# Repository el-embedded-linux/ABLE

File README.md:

PROJECT ABLE(Always Bicycle LifE)
=============================

Cycling is a great exercise. However, riding byclces outdoor is sometimes dangerous and difficult due to a bad weather or lack of bike infrastructures. Our project starts to solve those problems. We make a smart bicycle kit which can be equipped on a bicycle and let people can ride it both indoor and outdoor safely. With our kit incorporates Arduino, Raspberry Pi and VR, you can enjoy cycling anytime, anywhere.

When indoors, you can ride your bike fixed by rollers using VR. A lead switch and a pressure seonsor of Arduino deliver state of the bike to VR. When outdoors, you can use matrix LEDs and bar LEDs to use turn signal lights, so that you can ride more safely. In addition, this can replace smart phone applications, which provide unncessary information about bicycles, as ring LEDs and OLEDs can navigate or display speed, time, group riding information, heart rating etc. You can also prevent bike thefts by turning on and off your kit with fingerprint identification security system.

 youtube link

Field
-------------------
 - [IoT](https://github.com/Moerai/2018EL/tree/master/IoT)
 - [VR](https://github.com/Moerai/2018EL/tree/master/VR)
 - [Android](https://github.com/Moerai/2018EL/tree/master/android)

Thank you for your interest in our project.

This project is owned by the club EL of Dongyang Mirae University.

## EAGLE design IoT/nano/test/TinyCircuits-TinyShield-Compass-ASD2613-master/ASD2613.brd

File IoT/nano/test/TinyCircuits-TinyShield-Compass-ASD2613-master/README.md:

# TinyCircuits TinyShield Compass Board
# ASD2613 Rev1

These are the design files for the TinyCircuits ASD2613 Rev 1 PCB.  This is a TinyShield board (Square Version, 20mm x 20mm, or Circular 20mm diameter) that has a Honeywell HMC5883L compass, local power supply and level shifters to connect between the TinyDuino and the accelerometer. 

Format is in Cadsoft Eagle format - Eagle version 6.2 was used for the original design.

For more infomation on this, check out the product page at Tiny-Circuits.com:  https://tiny-circuits.com/tiny-shield-compass.html

#License:

Design by TinyCircuits.
All design files are released under the Creative Commons Attribution Share-Alike 3.0 License, see the following link for details: http://creativecommons.org/licenses/by-sa/3.0

All text above must be included in any redistribution or derived design

This project uses designs and concepts developed as part of the Arduino project and the LilyPad project.  The TinyCircuits design files themselves (schematics, PCB and libraries) are not directly derived from these works' design files and have been created new, however the concepts and basic architecture behind the TinyDuino and TinyLily products are derived and we thank the hard work of the organizations below for their contributions to open-source hardware:
  
Original Arduino Uno Design by Team Arduino

LilyPad Arduino Design by Leah Buechley and Sparkfun Electronics

Please support the open-source hardware community 

3? ????? Compass Value? ??? ??? ???

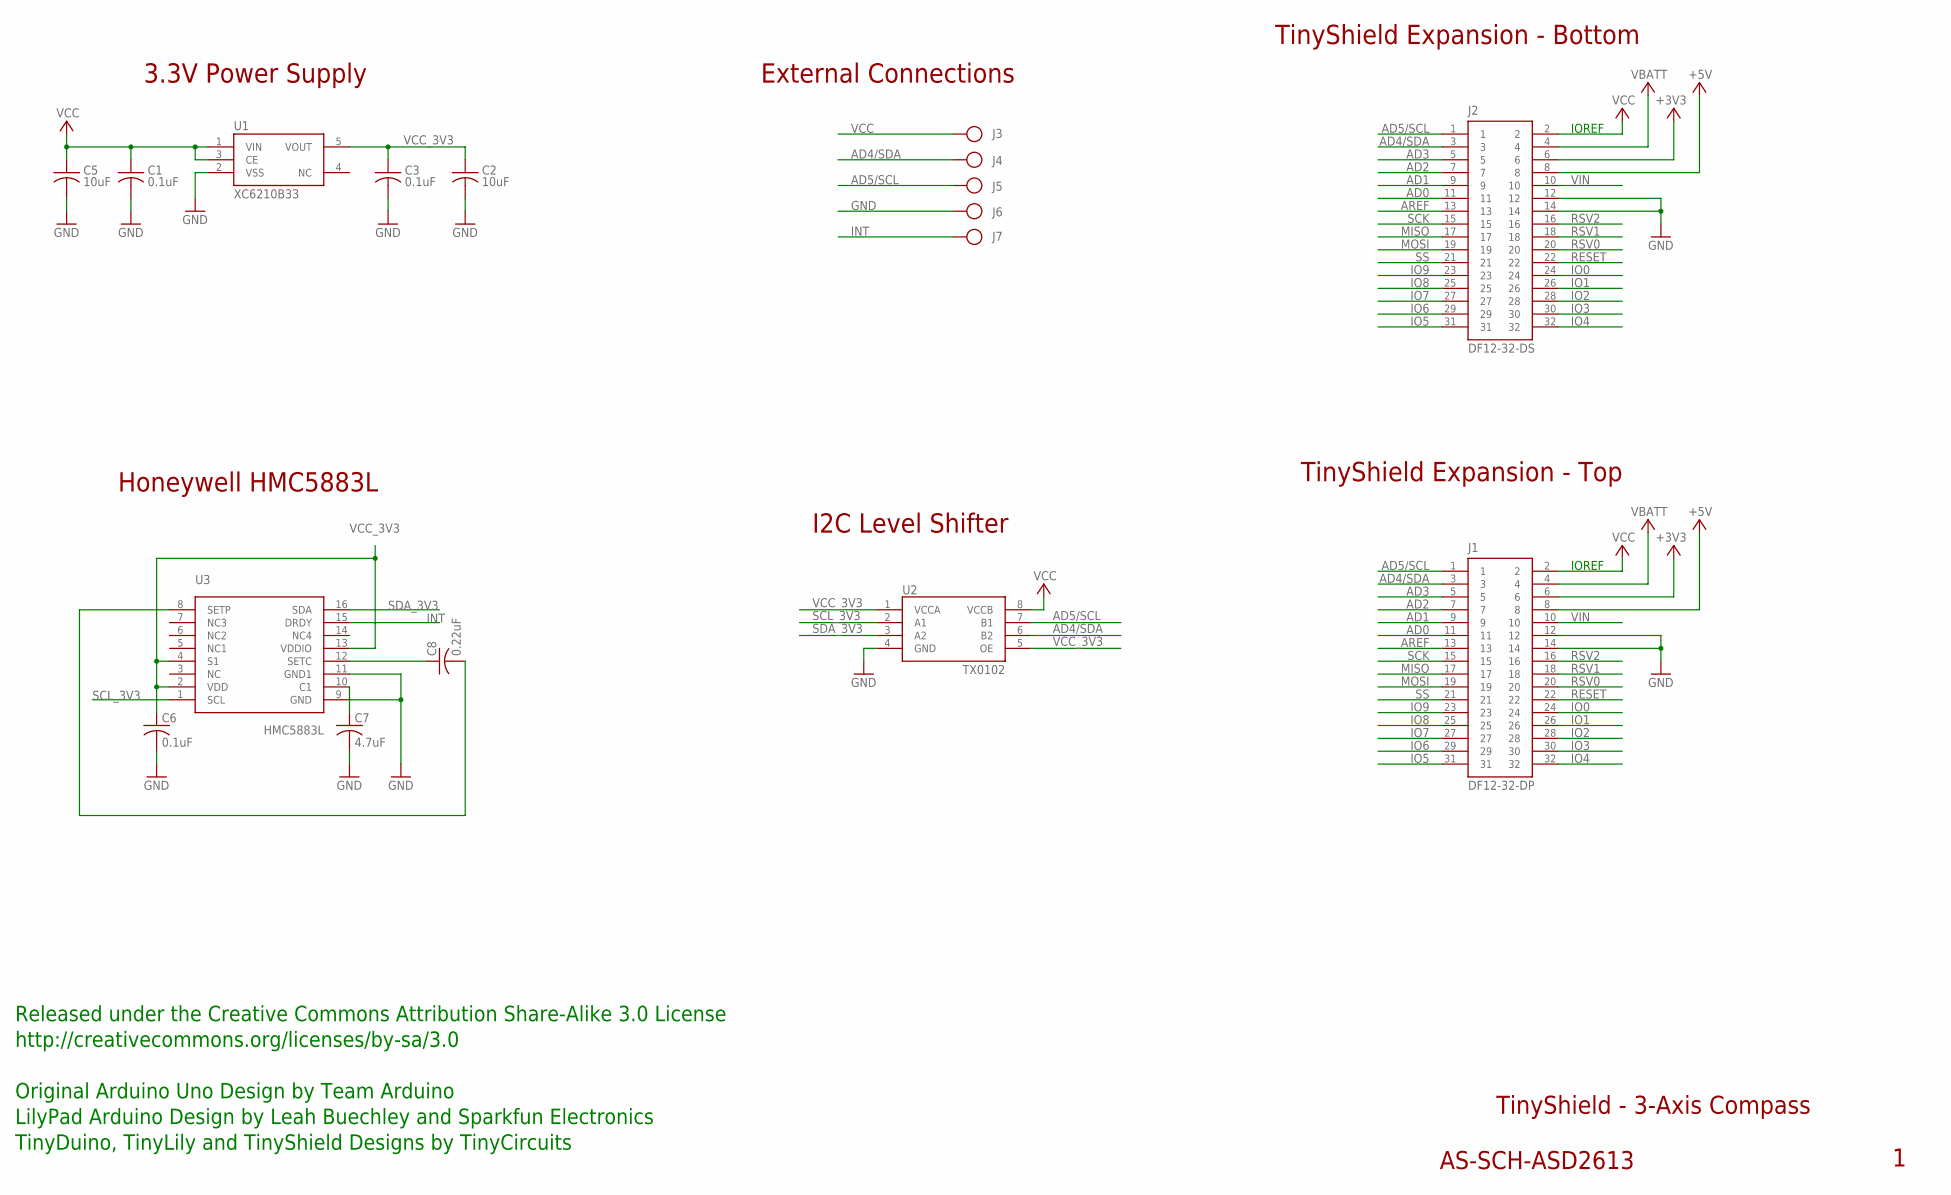
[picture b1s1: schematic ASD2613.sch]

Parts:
C1, C3: 0.1uF; C0402; PARTNO AS-ITM-00008
C2: 10uF; C0805; PARTNO AS-ITM-00045
C5: 10uF; C0805
C6: 0.1uF; C0402
C7: 4.7uF; C0603
C8: 0.22uF; 0402
J1: DF12-32-DP; PARTNO AS-ITM-00015
J2: DF12-32-DS; PARTNO AS-ITM-00012
J3, J4, J5, J6, J7: PIN_1X.1"; 1X.1"
U1: XC6210B33; SOT-25
U2: TX0102; DQE(R-PX2SON-N8)
U3: HMC5883L

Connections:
+3V3: J1.6, J2.6
+5V: J1.8, J2.8
AD0: J1.11, J2.11
AD1: J1.9, J2.9
AD2: J1.7, J2.7
AD3: J1.5, J2.5
AD4/SDA: J1.3, J2.3, J4.1, U2.6 (B2)
AD5/SCL: J1.1, J2.1, J5.1, U2.7 (B1)
AREF: J1.13, J2.13
GND: C1.2, C2.2, C3.2, C5.2, C6.2, C7.2, J1.12, J1.14, J2.12, J2.14, J6.1, U1.2 (VSS), U2.4 (GND), U3.9 (GND), U3.11 (GND1)
INT: J7.1, U3.15 (DRDY)
IO0: J1.24, J2.24
IO1: J1.26, J2.26
IO2: J1.28, J2.28
IO3: J1.30, J2.30
IO4: J1.32, J2.32
IO5: J1.31, J2.31
IO6: J1.29, J2.29
IO7: J1.27, J2.27
IO8: J1.25, J2.25
IO9: J1.23, J2.23
MISO: J1.17, J2.17
MOSI: J1.19, J2.19
unnamed: C8.2, U3.8 (SETP)
unnamed: C8.1, U3.12 (SETC)
unnamed: C7.1, U3.10 (C1)
RESET: J1.22, J2.22
RSV0: J1.20, J2.20
RSV1: J1.18, J2.18
RSV2: J1.16, J2.16
SCK: J1.15, J2.15
SCL_3V3: U2.2 (A1), U3.1 (SCL)
SDA_3V3: U2.3 (A2), U3.16 (SDA)
SS: J1.21, J2.21
VBATT: J1.4, J2.4
VCC: C1.1, C5.1, J1.2, J2.2, J3.1, U1.1 (VIN), U1.3 (CE), U2.8 (VCCB)
VCC_3V3: C2.1, C3.1, C6.1, U1.5 (VOUT), U2.1 (VCCA), U2.5 (OE), U3.2 (VDD), U3.4 (S1), U3.13 (VDDIO)
VIN: J1.10, J2.10

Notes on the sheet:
TinyShield Expansion - Bottom
TinyShield - 3-Axis Compass
AS-SCH-ASD2613
TinyShield Expansion - Top
IOREF
Released under the Creative Commons Attribution Share-Alike 3.0 License
http://creativecommons.org/licenses/by-sa/3.0
LilyPad Arduino Design by Leah Buechley and Sparkfun Electronics
TinyDuino, TinyLily and TinyShield Designs by TinyCircuits
Original Arduino Uno Design by Team Arduino
External Connections
3.3V Power Supply
I2C Level Shifter
Honeywell HMC5883L

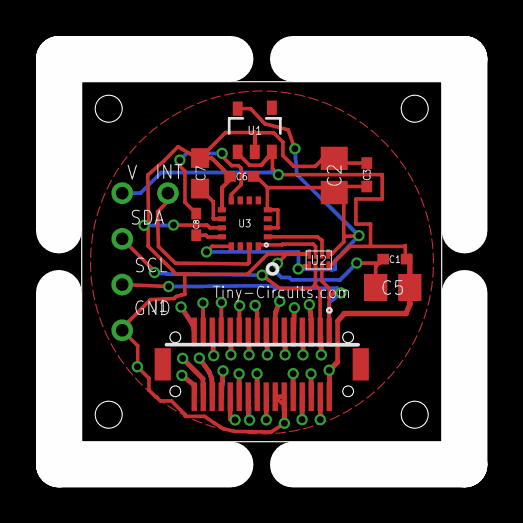
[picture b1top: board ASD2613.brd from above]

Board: 2 copper layers, 20.0 x 20.0 mm, 18 parts (1 on the bottom side), 38 nets.

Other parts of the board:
U$1: DOCFIELD-TINYCIRCUITS-PCB

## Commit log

2018-04-27 readme
2018-04-27 directory
2018-04-29 수정이가 표현을 잡아줬음
2018-05-02 Update README
    Authentication
2018-05-07 mpu9250 row data받아오기 성공
2018-05-10 안드로이드 현재 구현 사항 commit
    로그인 - 이메일&패스워드, 페이스북, 구글
    친구 - 친구목록, 유저목록
    데이터베이스 USER,FRIEND 추가
2018-05-11 Create Map
2018-05-11 설원맵 프로젝트 입니다
    오브젝트가 많아서 그런지 용량이 꽤 크네요.
    캐릭터 오브젝트는 없습니다.
    오직 맵 만 만든 프로젝트 입니다.
2018-05-11 Map Project update
    .
2018-05-11 README Update
2018-05-15 안드로이드 주석 commit
    각 클래스별 주석 첨부
2018-05-15 안드로이드 티맵 commit
    기본적인 맵 구현과 자동차 경로
2018-05-16 안드로이드 헬스케어 commit
    헬스케어 UI/UX 와 datepicker, 칼로리 소모량 반환
2018-05-17 RingLED 지자기센서 연동
2018-05-17 지자기센서 RingLED 연동 (지자기센서가 바라보고 있는 방향을 RingLED에서 출력해줌)
2018-05-18 Reed_switch 성공, mpu9250다른 코드 커밋합니다.
2018-05-18 블루투스 서버
    안드로이드와 라즈베리파이 통신에 사용될 블루투스 서버 파일입니다.
2018-05-22 DB연동성공
    UI, DB, 캐릭터 뼈대구현
2018-05-29 print 앞에 시리얼이 빠져있는거 확인함
2018-05-29 gy-85 success
2018-05-30 안드로이드 네비게이션 commit
    네비게이션에 출발, 목적지 마커와 라인 생성
2018-05-30 IoT 디렉토리 변경 및 Ring9250의 Todo list 작성
2018-05-30 RingLED와 MPU9250으로 나침반 만들기 성공&&0~360의 범위를 벗어난 값들을 처리했음 compass.ino추가
2018-05-30 폴더 위치 변경
2018-06-01 지자기센서의 모를꺼 같던 비밀을 풀었음
2018-06-01 VRNANO
2018-06-01 nanoLED
2018-06-01 라즈베리파이 아두이노 통신성공
2018-06-03 UI개선, 게임종료시 DB저장 구현
    DB저장시의 날짜를 추가했습니다.
    플레이타임과 같이 저장되는 칼로리와 주행거리데이터는 임의의 값을 저장시킨것입니다.
2018-06-05 리드스위치, 아두니티 합친것
    ㅈㄱㄴ
2018-06-06 아두이노 IoT부분 커밋
2018-06-06 아두이노 IoT부분 커밋2
2018-06-06 프로토타입용 OLED코드입니다.
2018-06-07 리드스위치 속도 측정 포트 변경
2018-06-07 Arduino prototype
2018-07-12 Server
    bluethooth server with android and Usb Serial connection to arduino
2018-07-14 adding files
2018-07-18 VR Arduino 통신
2018-07-22 안드로이드 커밋
2018-07-22 레이아웃 수정, 네비게이션 테스트
2018-07-24 네비게이션 예상시간,거리, 버튼 추가 앱 강제종료 수정
2018-07-24 날씨 API 수정
2018-07-25 심박도센서 테스트, TFT테스트
2018-07-27 설산 수정 버전 업로드
    설산 수정버전
    기존의 도로를 삭제하고 지형의 높낮이를 조절해 자연스러운 도로제작
    설산 배치변경
2018-08-04 네비게이션 수정
2018-08-09 tftTest 확인 및 nanoVR새로운 버전
2018-08-09 TFT LCD모니터와 ReedSW연결, 자석으로 실험아직 못해봄
2018-08-09 tft LCD 핀 정의 안해서 다시하고 코드정리함
2018-08-09 버튼을 누르면 speed와 distance가 바뀐다. but 실시간이 아니라는 이슈가 있다.
2018-08-09 reed sw로 실시간으로 값을 입력받고 LCD에 버튼을 누르면 바로 speed와 distance를 바꿔줄 수 있게 적용
2018-08-09 matrix, bar LED, press sensor 연결방법 모색중...
2018-08-09 nanoVR완성... 버튼과 간섭 이슈 존재
2018-08-10 firebase cloud messaging 을 이용한 채팅 구현
2018-08-10 compile 에러 개선을 위한 gms 버전 업그레이드
2018-08-12 개인정보 약관 동의 미체크시 토스트, 스위치 삭제, 유저목록에 자신 미포함
2018-08-12 헬스케어 레이아웃 추가
2018-08-12 헬스케어 레이아웃 버튼위치변경
2018-08-13 헬스케어 달력 및 서클프로그레스바 라이브러리 적용
2018-08-13 openWeatherMap api 를 받아 위경도값을 통해 날씨와 최고,최저기온 표시
2018-08-14 nanoVR_new 만듬
2018-08-14 내정보에 goal 추가 및 디자인 변경, fab 버튼에 타이틀 추가
2018-08-14 사용자의 목표와 이동거리에 따라 circleProgressbar 갱신
2018-08-15 16일 자체 검사 대비
2018-08-15 웹뷰 수정, 노티 추가, 네비게이션 ui 변경
2018-08-16 친구목록에서 터치시 친구의 profile 전환
2018-08-17 splash 화면 추가, 헬스케어 에러 개선
2018-08-18 상민이형이랑 수정이가 같이 만들던거
2018-08-19 splash 이미지, 차트 샘플 추가
2018-08-19 22일에 시연용 후미등, 나침반, 속도계 제작중
2018-08-19 recode 차트 추가,친구 프로필 수정
2018-08-20 심박동샌서 연동
2018-08-20 친구프로필 ui 수정
2018-08-20 친구리스트 ui 수정
2018-08-20 액티비티 타이틀 수정
2018-08-21 발표준비 완료
2018-08-22 경로 변경
2018-08-24 ui 개선, 노티바 오레오 대응
2018-08-24 프래그먼트 호출 수정, 이미지 파일 위치변경
2018-08-26 gitignore 추가
2018-08-26 UserModel 수정
2018-08-26 프로필 이미지 변경 추가, 레이아웃 수정
2018-08-27 nav_header_main 유저 정보 불러와서 이미지,텍스트 변경
2018-08-28 왜 raw파일을 먼저 실행 시켜야 지자기센서가 되는지 모르겠다...
2018-08-28 지금까지 한거 커밋
2018-09-05 navigation을 activity 구조로 변경
2018-09-05 navigation layout 수정, drawable resource 추가
2018-09-06 종료버튼 추가, 방향지시 추가
2018-09-10 방향안내 별도 스레드 처리
2018-09-10 메인 액티비티에서 목적지 설정 버튼 클릭시 네비게이션 액티비티로 이동
2018-09-10 그룹라이딩 맵 선택 버튼 추가 및 클릭시 네비게이션 액티비티 이동
2018-09-11 단체채팅방에서 맵 이동 및 목적지 설정 후 공유 버튼 클릭시 채팅 저장
2018-09-11 채팅 메세지 내부 시작 버튼 클릭시 네비게이션 액티비티로 이동
2018-09-11 앱종료 현상 개선
2018-09-11 Optimize imports
2018-09-12 DataReference 중복 코드 제거
2018-09-13 단체채팅 메세지 버튼 클릭시 그룹라이딩 네비게이션으로 이동
2018-09-13 아두이노에서 라즈베리파이로 데이터 보내기
2018-09-14 네비게이션 레이아웃 수정
2018-09-14 메세지 버튼 클릭시 navigationActivity 경로 표시
2018-09-17 NavigationActivity 오른쪽 drawer 생성 시도
2018-09-17 NavigationActivity toolbar 왼쪽에 메뉴 아이콘 생성
2018-09-18 네비게이션 drawer 디자인 수정
2018-09-18 그룹라이딩 추가
2018-09-19 앱 종료 에러 수정
2018-09-19 nano_IoT_last 생성
2018-09-19 nano_VR_last 생성
2018-09-20 tftLCD TEST
2018-09-21 전체 초기화 없이 TFTLCD 값만 변경
2018-09-22 여기 거의 다 만들어 둔게 있었어
2018-09-22 tftLCD 딜레 없는 출력 성공
2018-09-22 테스트 한 것들 정리해둠
2018-09-25 채팅방 생성 완료시 selectFriendActivity 종료
2018-09-25 로딩 화면 추가
2018-09-25 개인 채팅 생성 에러 수정
2018-09-25 유저의 저장된 주소로 날씨 변경
2018-09-25 네비게이션 주소 검색시 지번주소에 null 제거
2018-09-25 MessageActivity 코드 수정
2018-09-25 로그인되지 않아도 메인화면에서 날씨 출력, 앱시작시 위치정보 권한 허가 요청
2018-09-26 그룹라이딩시 참가한 유저리스트 중복 수정
2018-09-30 시리얼통신 안드로이드-라즈베리-아두이노 블루투스 통신 개발 완료
2018-10-01 주석 추가
2018-10-04 test
2018-12-04 GPS값 문자열형식 수정
2018-12-11 라즈베리파이 bluetooth 통신 개발완료
2018-12-11 아두이노 나노 VR 파트 개발완료
2018-12-11 VR 최종 컨텐츠 제작및 버그 수정
2018-12-11 필요없는거 삭제
2019-08-13 Update README.md
    youtube video plus
2019-08-13 Update README.md
    image was corrupted.
2019-08-13 Update README.md
    change video label to youtube link
